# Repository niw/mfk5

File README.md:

mfk5
====

A prototype keyboard that contains enough features to make a full size
split keyboard. mfk5 is My first keyboard, 5 keys.

This project has concluded and there is a successor, a real full size
split keyboard project, [mfk60](https://github.com/niw/mfk60).

Original Goal
-------------

The goal is testing a design for each component, footprint, and
production process for layered plate design.

- Use [Gateron Low-Profile switches](https://gateron.com/products/gateron-ks-33-low-profile-switch-set?VariantsId=10275)
  on [Hot-Swap socket](https://gateron.com/products/gateron-low-profile-switch-hot-swap-pcb-socket?VariantsId=10234).
- Use [Gateron Low-Profile 2U stabilizer](https://gateron.com/products/gateron-low-profile-plate-mounted-stabilizer?VariantsId=10478),
  which is top plate mount.

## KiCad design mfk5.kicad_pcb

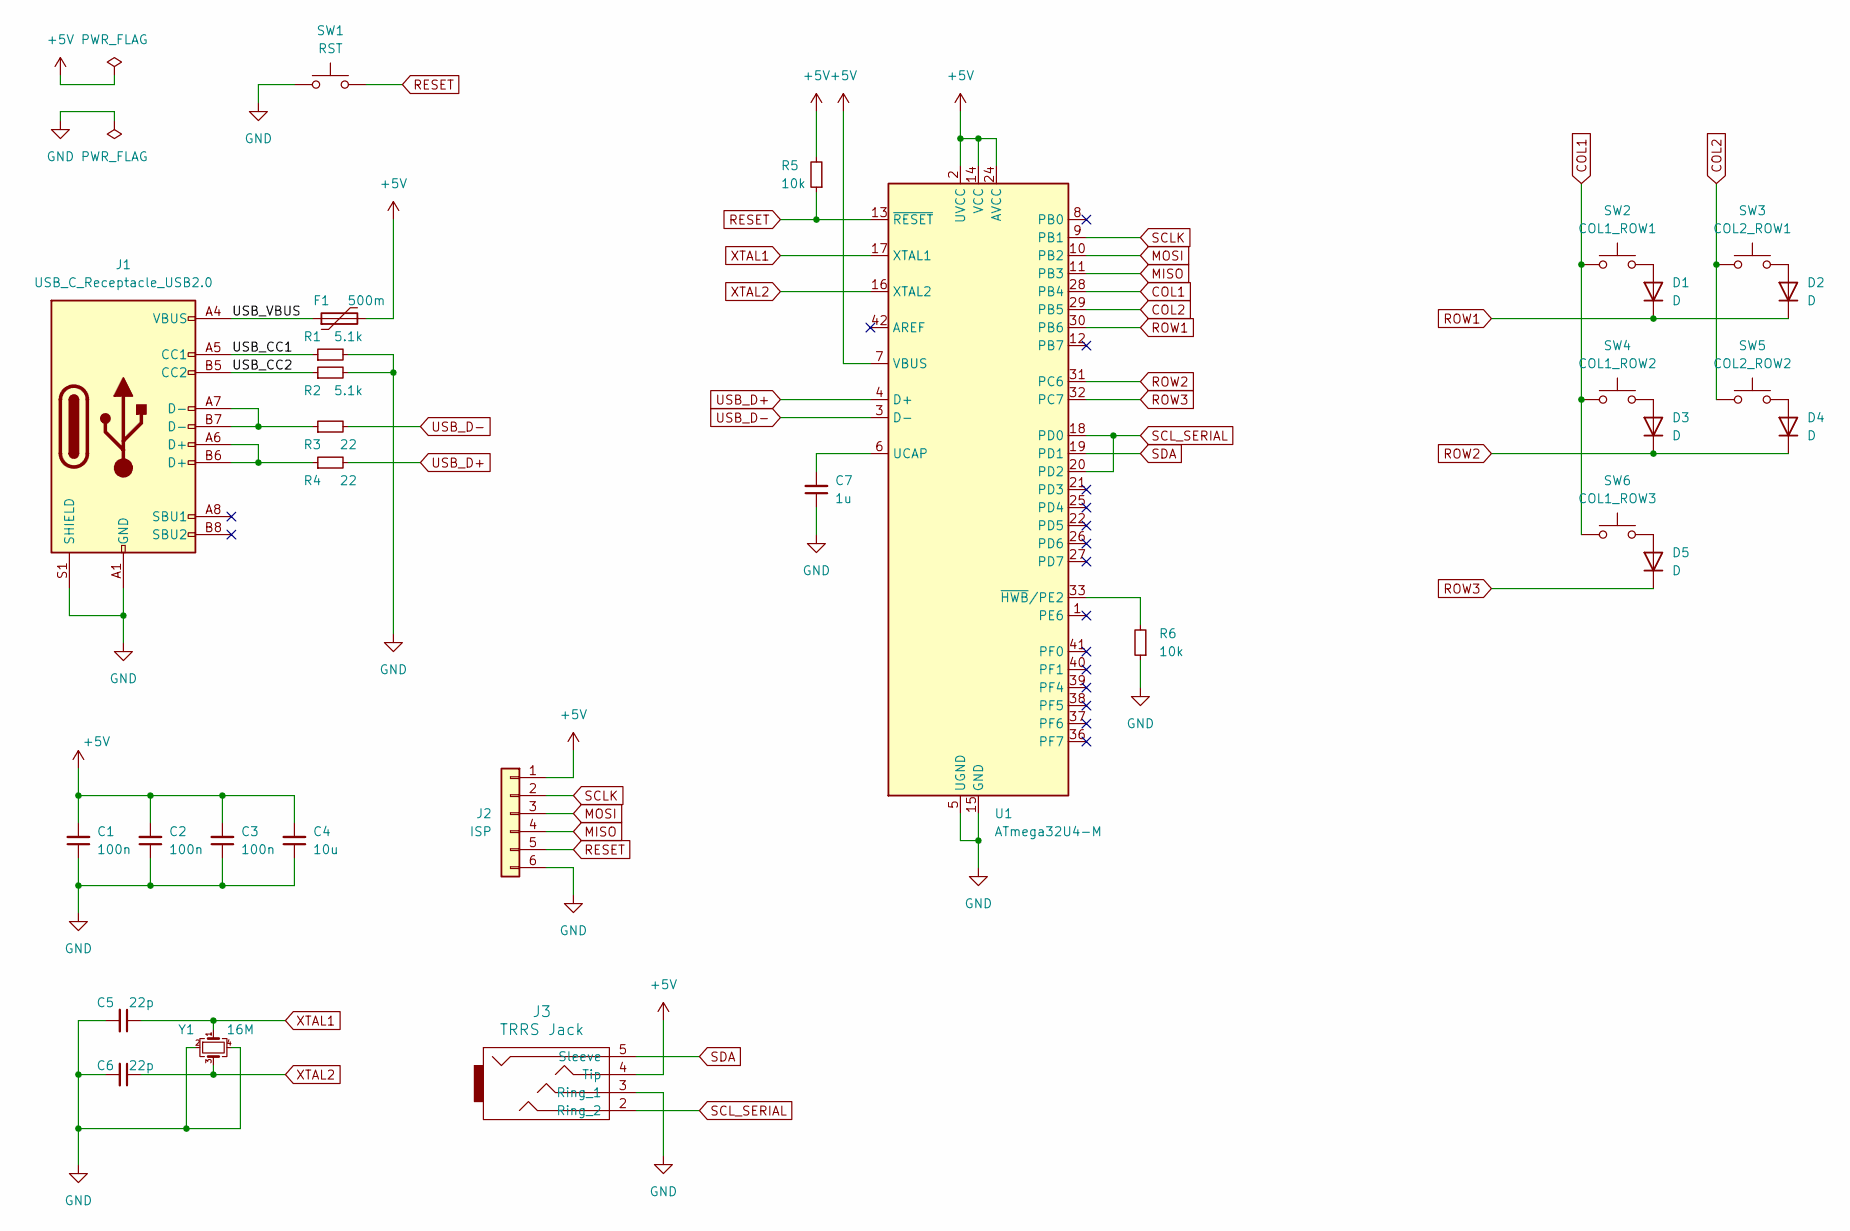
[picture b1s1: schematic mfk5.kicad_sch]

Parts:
C1, C2, C3: 100n; C_0805_2012Metric_Pad1.18x1.45mm_HandSolder; LCSC C49678
C4: 10u; C_0805_2012Metric_Pad1.18x1.45mm_HandSolder; LCSC C15850
C5, C6: 22p; C_0805_2012Metric_Pad1.18x1.45mm_HandSolder; LCSC C1804
C7: 1u; C_0805_2012Metric_Pad1.18x1.45mm_HandSolder; LCSC C28323
D1, D2, D3, D4, D5: D; D_SOD-123; LCSC C81598
F1: 500m; Fuse_1206_3216Metric_Pad1.42x1.75mm_HandSolder; LCSC C75464
J1: USB_C_Receptacle_USB2.0; USB_C_Receptacle_HRO_TYPE-C-31-M-12; LCSC C2982555
J2: ISP; PinHeader_1x06_P2.54mm_Vertical
J3: TRRS Jack; TRRS_Jack_3.5mm_PJ320A
R1, R2: 5.1k; R_0805_2012Metric_Pad1.20x1.40mm_HandSolder; LCSC C27834
R3, R4: 22; R_0805_2012Metric_Pad1.20x1.40mm_HandSolder; LCSC C17561
R5, R6: 10k; R_0805_2012Metric_Pad1.20x1.40mm_HandSolder; LCSC C17414
SW1: RST; SW_Push_3.5x6mm_THT
SW2: COL1_ROW1; Gateron_Low_Profile_Socket
SW3: COL2_ROW1; Gateron_Low_Profile_Socket
SW4: COL1_ROW2; Gateron_Low_Profile_Socket
SW5: COL2_ROW2; Gateron_Low_Profile_Socket
SW6: COL1_ROW3; Gateron_Low_Profile_Socket_Stabilizer_2U
U1: ATmega32U4-M; QFN-44-1EP_7x7mm_P0.5mm_EP5.2x5.2mm; LCSC C112161
Y1: 16M; Crystal_SMD_3225-4Pin_3.2x2.5mm_HandSoldering; LCSC C255949

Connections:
+5V: C1.2, C2.2, C3.2, C4.2, F1.2, J2.1, J3.4 (Tip), R5.2, U1.2 (UVCC), U1.7 (VBUS), U1.14 (VCC), U1.24 (AVCC), U1.34 (VCC), U1.44 (AVCC)
/USB_CC1: J1.A5 (CC1), R1.1
/USB_CC2: J1.B5 (CC2), R2.1
/USB_VBUS: F1.1, J1.A4 (VBUS), J1.A9 (VBUS), J1.B4 (VBUS), J1.B9 (VBUS)
COL1: SW2.1, SW4.1, SW6.1, U1.28 (PB4)
COL2: SW3.1, SW5.1, U1.29 (PB5)
GND: C1.1, C2.1, C3.1, C4.1, C5.2, C6.2, C7.1, J1.A1 (GND), J1.A12 (GND), J1.B1 (GND), J1.B12 (GND), J1.S1 (SHIELD), J2.6, J3.3 (Ring_1), R1.2, R2.2, R6.1, SW1.2, U1.5 (UGND), U1.15 (GND), U1.23 (GND), U1.35 (GND), U1.43 (GND), U1.45 (GND), Y1.2, Y1.4
MISO: J2.4, U1.11 (PB3)
MOSI: J2.3, U1.10 (PB2)
unnamed: D1.2 (A), SW2.2
unnamed: D2.2 (A), SW3.2
unnamed: D3.2 (A), SW4.2
unnamed: D4.2 (A), SW5.2
unnamed: D5.2 (A), SW6.2
unnamed: J1.A6 (D+), J1.B6 (D+), R4.1
unnamed: J1.A7 (D-), J1.B7 (D-), R3.1
unnamed: C7.2, U1.6 (UCAP)
unnamed: R6.2, U1.33 (~HWB/PE2)
RESET: J2.5, R5.1, SW1.1, U1.13 (~RESET)
ROW1: D1.1 (K), D2.1 (K), U1.30 (PB6)
ROW2: D3.1 (K), D4.1 (K), U1.31 (PC6)
ROW3: D5.1 (K), U1.32 (PC7)
SCLK: J2.2, U1.9 (PB1)
SCL_SERIAL: J3.2 (Ring_2), U1.18 (PD0), U1.20 (PD2)
SDA: J3.5 (Sleeve), U1.19 (PD1)
USB_D+: R4.2, U1.4 (D+)
USB_D-: R3.2, U1.3 (D-)
XTAL1: C5.1, U1.17 (XTAL1), Y1.1
XTAL2: C6.1, U1.16 (XTAL2), Y1.3

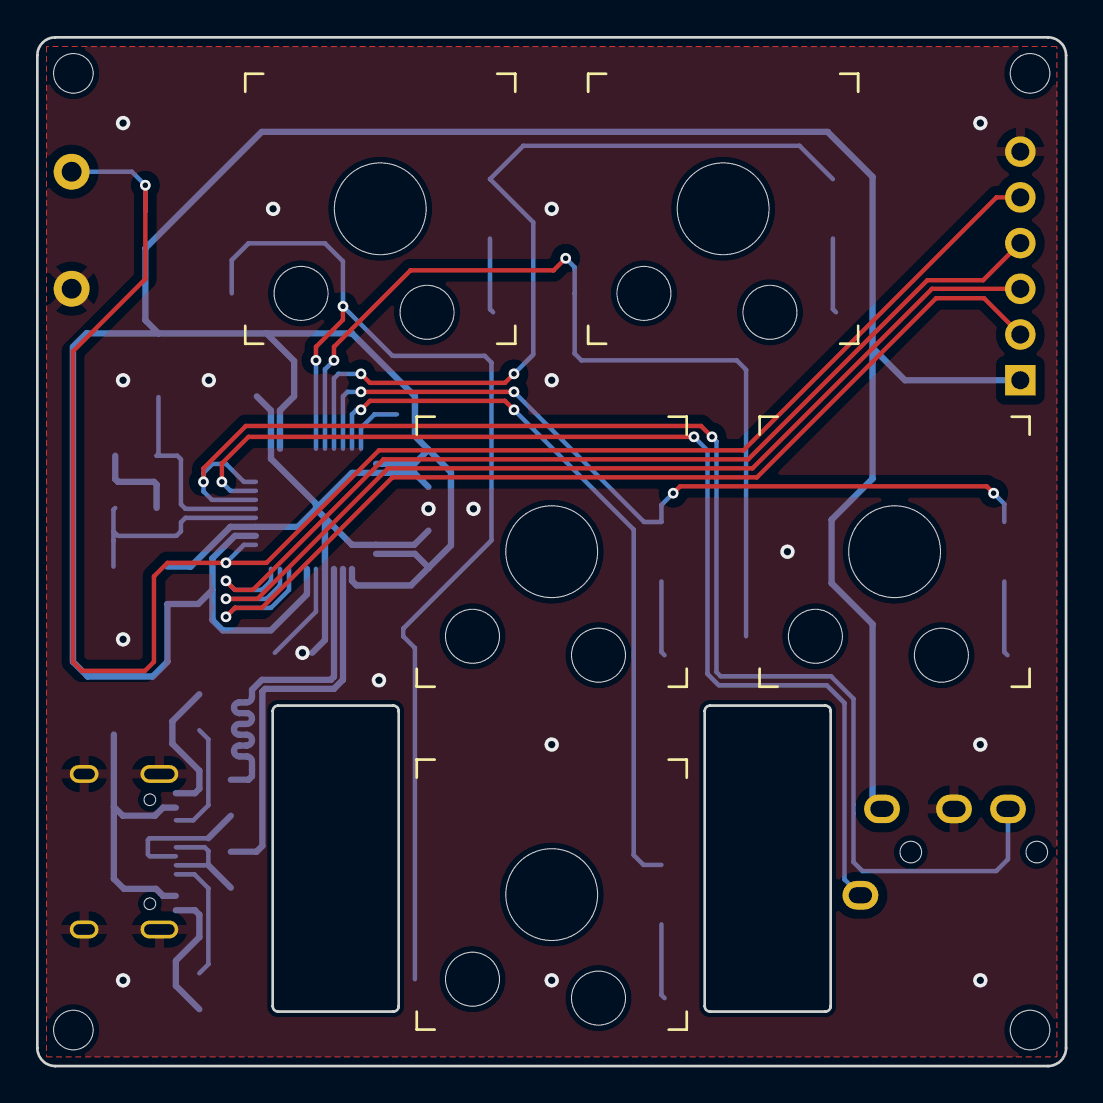
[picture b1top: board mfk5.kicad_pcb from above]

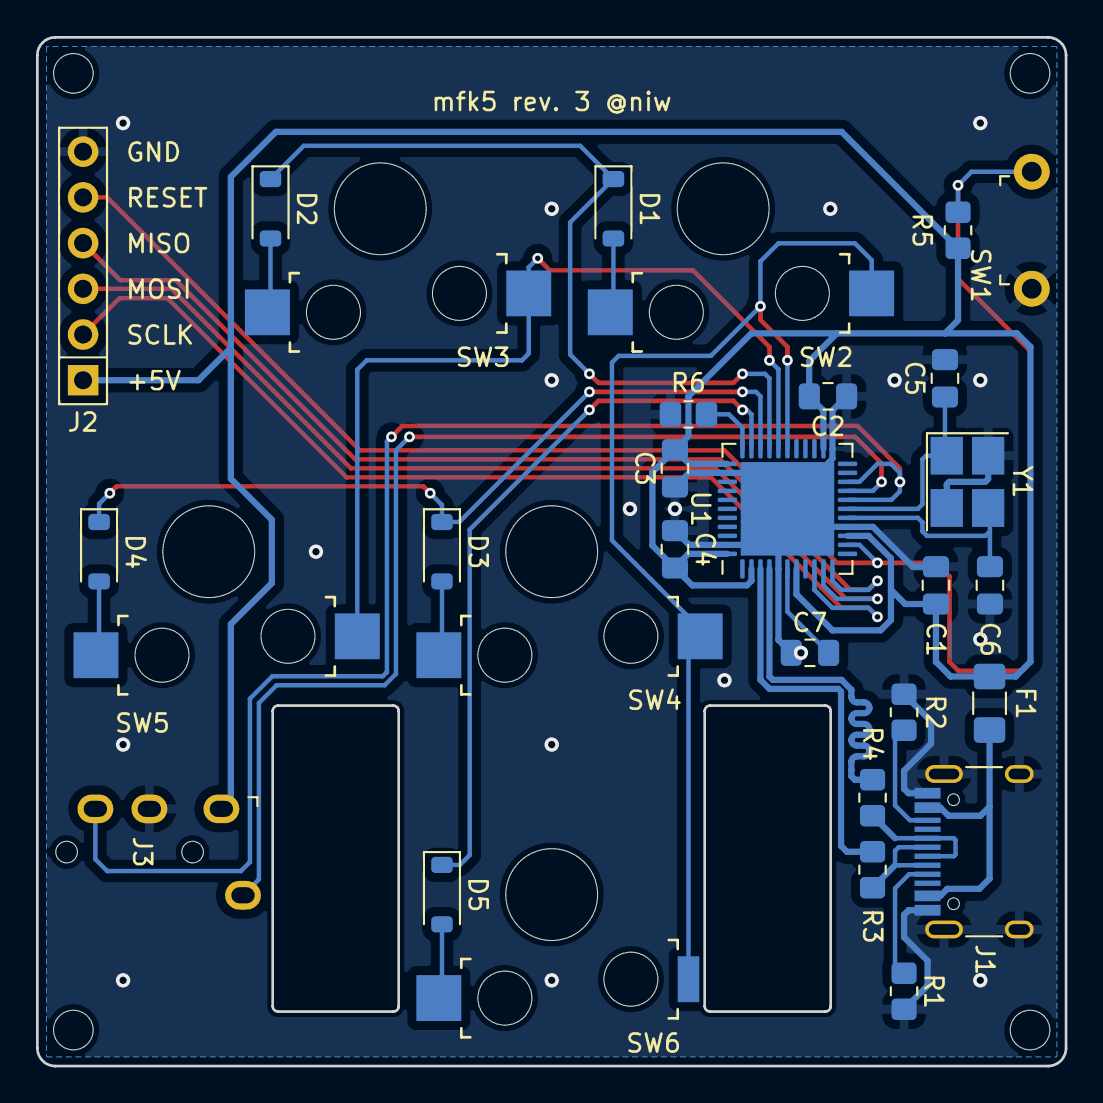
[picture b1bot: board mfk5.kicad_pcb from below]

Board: 2 copper layers, 57.2 x 57.2 mm, 34 parts (25 on the bottom side), 29 nets.

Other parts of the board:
MH1, MH2, MH3, MH4: MountingHole_2.2mm_M2

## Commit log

2023-06-20 Initial.
2023-06-21 Add mfk5.
    Rev. 1, Initial submit to JLCPCB.
2024-01-25 Add Gateron Low Profile for middle plate.
2024-01-25 Add middle plate.
2024-01-25 Update Gateron Low Profile with Stabilizer.
2024-01-25 Update mfk5 layout.
2024-01-25 Rename panel to plate.
2024-01-25 Remove Orders from ignores.
2024-01-25 Increment revision.
    - Rev. 2
    - Update title blocks.
2024-01-25 Remove unused Pro Micro symbol and footprint.
2024-01-25 Add Kikit and panelization scripts.
2024-01-25 Add ATmega32u4 and related components.
    Stop using Pro Micro, going to use PCBA to SMT components.
2024-01-25 Add README and LICENSE.
